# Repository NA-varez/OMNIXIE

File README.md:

# OMNIXIE
Nixie driver board to enable easy inclusion of a Nixie tube into projects. One common driver board to support a wide range of Nixie INdicator Tubes. I love modularity!

Initial sketches, ideas, original project intent was just a nixie clock. But I hated the feeling of desigingn a nixie clock with the nixie driver circuitry as single use for just a clock, when really you should be able to drive a nixie tube anywehere you'd like for displaying numbers. So that's where this inspiration came from

ALSO cnlohr's cnixxie. Particularly his MCU of choice ch32v003 and the accompanying library ch32v003fun and rv003usb inspired the digitally controlled flyback he uses in his design. Really in hopes of learning some skills he demonstrated in his youtube vide.

OMNIXIE is omni beause all of its OMNIXIE_HATs share a common hardware interface to the nixie driver board. Since nixie tubes wildly vary in their footprint, its nice to share a common hardware connection between them all thats what makes it omni. 

The real guts is the ddriver board.
Should be minimal in size such that it doesnt add any more difficult in creating some case for the nixie tube.
Should be relatively efficient like 90% efficiency on the flyback onverter
Should be programmable 
  There should be a software package that comes with the hardware that could easily spin up different functionality

The default program should allow the user of the board to immediatly get the devices to display a synchronized clock.
Via some qwiic connectors. Might have to be a custom i2c interface.

A flyback seemed to be the most suitable approach because of the smallest amount of parts needed for it.

WORK IN PROGRESS.

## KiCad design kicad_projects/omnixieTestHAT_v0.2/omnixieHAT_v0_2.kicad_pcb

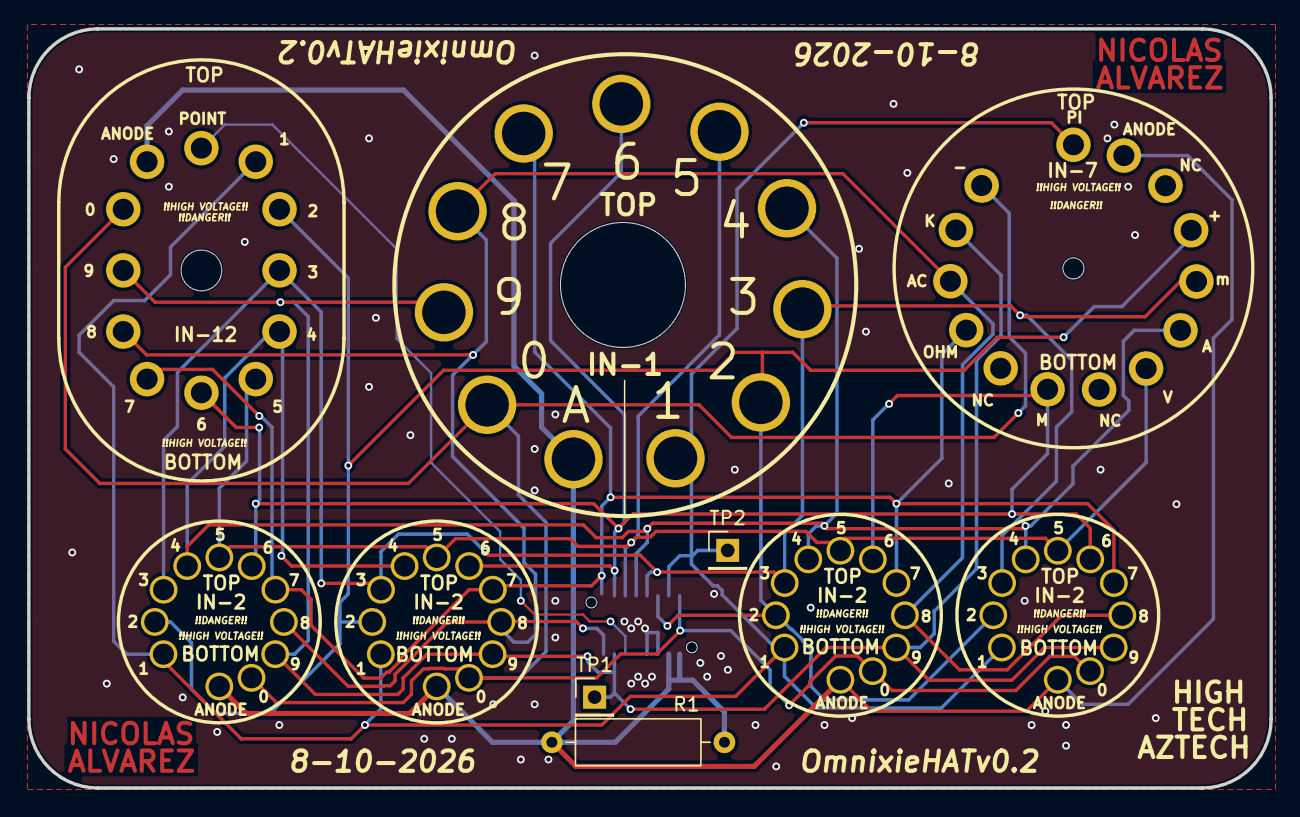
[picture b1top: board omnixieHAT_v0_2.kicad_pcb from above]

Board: 2 copper layers, 91.4 x 55.9 mm, 11 parts (1 on the bottom side), 13 nets.

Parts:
J1: IL-WX-16PB-VF-B-E1000E; IL-WX-16PB-VF-B-E1000E-PINS
N1: IN-1_NIXIE_v1
N2, N5, N6, N7: IN-2
N3: IN-7
N4: IN-12BORIGINAL; IN-12A Nixie
R1: R; R_Axial_DIN0309_L9.0mm_D3.2mm_P12.70mm_Horizontal
TP1: 9; PinHeader_1x01_P2.54mm_Vertical
TP2: 1; PinHeader_1x01_P2.54mm_Vertical

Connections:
CATH0: J1.1, N1.0, N2.0, N3.14 (-), N4.0, N5.0, N6.0, N7.0
CATH1: J1.2, N1.1 (9), N2.1 (9), N3.1 (PI), N4.1, N5.1 (9), N6.1 (9), N7.1 (9), TP2.1 (1_1)
CATH2: J1.3, N1.2 (8), N2.2 (8), N3.4 (+), N4.2, N5.2 (8), N6.2 (8), N7.2 (8)
CATH3: J1.4, N1.3 (7), N2.3 (7), N3.5 (m), N4.3, N5.3 (7), N6.3 (7), N7.3 (7)
CATH4: J1.5, N1.4 (6), N2.4 (6), N3.6 (A), N4.4, N5.4 (6), N6.4 (6), N7.4 (6)
CATH5: J1.6, N1.5, N2.5, N3.7 (V), N4.5, N5.5, N6.5, N7.5
CATH6: J1.7, N1.6 (4), N2.6 (4), N3.9 (M), N4.6, N5.6 (4), N6.6 (4), N7.6 (4)
CATH7: J1.8, N1.7 (3), N2.7 (3), N3.11 (OHM), N4.7, N5.7 (3), N6.7 (3), N7.7 (3)
CATH8: J1.9, N1.8 (2), N2.8 (2), N3.12 (AC), N4.8, N5.8 (2), N6.8 (2), N7.8 (2)
CATH9: J1.10, N1.9 (1), N2.9 (1), N3.13 (K), N4.9, N5.9 (1), N6.9 (1), N7.9 (1), TP1.1 (1_1)
CATHDP: J1.11, N4.DP
GND: J1.13, J1.14
HIGHVOLTAGE: J1.15, J1.16, N1.A, N2.A, N3.2 (A), N4.A, N5.A, N6.A, N7.A, R1.1, R1.2

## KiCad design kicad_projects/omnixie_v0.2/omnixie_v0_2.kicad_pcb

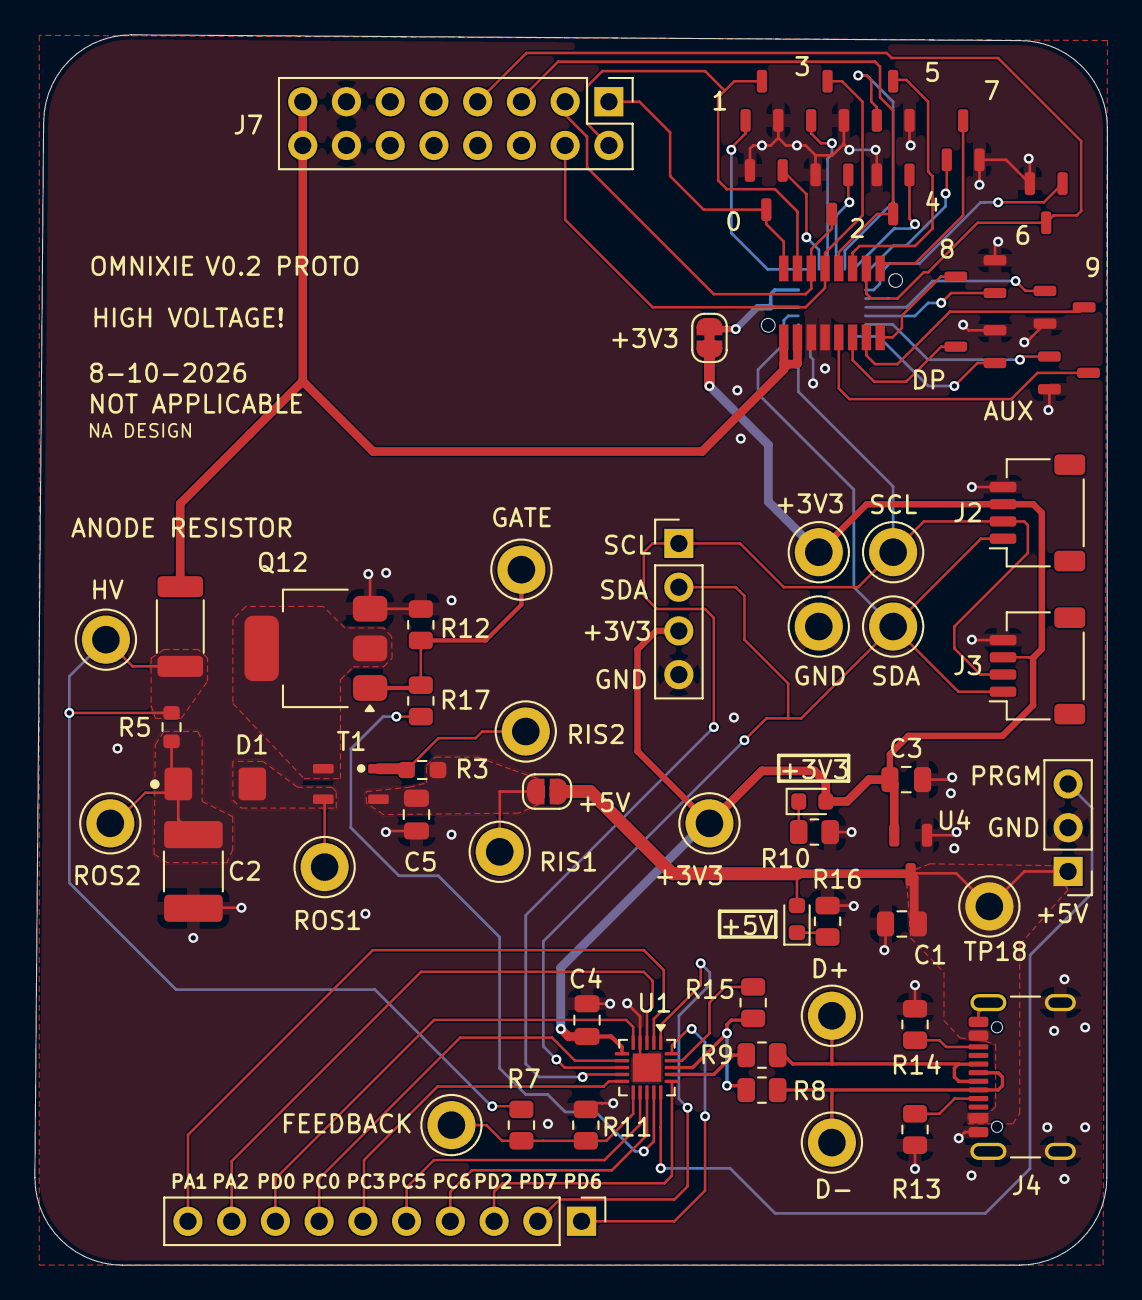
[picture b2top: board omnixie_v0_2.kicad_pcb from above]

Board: 2 copper layers, 62.3 x 71.5 mm, 64 parts (1 on the bottom side), 60 nets.

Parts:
+3V3, +3V3#2: 5005; TestPoint_Keystone_5005-5009_Compact
+5V: GREEN; LED_0603_1608Metric
C1: 10uF; C_0805_2012Metric
C2: 0.22uF; C_1812_4532Metric_Pad1.57x3.40mm_HandSolder
C3, C4, C5: 1uF; C_0805_2012Metric
D1: SK3200AFL-TP; SK3200AFL
D3: GREEN; LED_0603_1608Metric
D+: 5005; TestPoint_Keystone_5005-5009_Compact
D-: 5005; TestPoint_Keystone_5005-5009_Compact
GND: 5005; TestPoint_Keystone_5005-5009_Compact
J1: Conn_01x10; PinHeader_1x10_P2.54mm_Vertical
J2, J3: SM04B-SRSS-TB; JST_SH_SM04B-SRSS-TB_1x04-1MP_P1.00mm_Horizontal
J4: USB4105-GF-A; USB_C_Receptacle_GCT_USB4105-xx-A_16P_TopMnt_Horizontal
J5: Conn_01x04; PinHeader_1x04_P2.54mm_Vertical
J6: Conn_01x02; PinHeader_1x03_P2.54mm_Vertical
J7: Conn_02x08_Counter_Clockwise; PinHeader_2x08_P2.54mm_Vertical
J8: IL-WX-16S-VF-B-E1000E; IL-WX-16S-VF-B-E1000E-SOCKET
JP4: SMT_THERM_JMP; SolderJumper-2_P1.3mm_Bridged_RoundedPad1.0x1.5mm
JP5: TH_THERM_JMP; SolderJumper-2_P1.3mm_Open_RoundedPad1.0x1.5mm
Q0, Q1, Q2, Q3, Q4, Q5, Q6, Q7, Q8, Q9, Q10, Q11: BSS123; SOT-23-3-NO_SILK
Q12: STN1NK60ZL; SOT-223-MiddlePinDrain
R3: 10m; R_0603_1608Metric_Pad0.98x0.95mm_HandSolder
R5: 10m; R_0603_1608Metric
R6: 15k; R_2010_5025Metric
R7: 100k; R_0805_2012Metric
R8, R9: 47; R_0805_2012Metric
R10, R16: 30K; R_0805_2012Metric
R11, R12: 1k; R_0805_2012Metric
R13, R14: 5.1k; R_0805_2012Metric
R15: 1.5k; R_0805_2012Metric
R17: JUMPER; R_0805_2012Metric
RIS1: 5005; TestPoint_Keystone_5005-5009_Compact
SCL: 5005; TestPoint_Keystone_5005-5009_Compact
SDA: 5005; TestPoint_Keystone_5005-5009_Compact
T1: ATB322515-0110; ATB322515
TP6, TP8, TP11, TP12, TP13, TP14, TP18: 5005; TestPoint_Keystone_5005-5009_Compact
U1: CH32V003F4U6; QFN-20-1EP_3x3mm_P0.4mm_EP1.65x1.65mm
U3: PI4IOE5V6416ZDEX; PI4IOE5V6416ZDEX-TQFN24
U4: XC6206P332MR; SOT-23-3-NO_SILK

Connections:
+3V3: +3V3.1 (1_1), +3V3#2.1 (1_1), C3.1, C4.1, D3.2 (A), J2.3, J3.3, J5.3, JP4.1 (A), U1.6 (VDD), U4.2 (VO)
+3V3_JUMP: JP4.2 (B), U3.21 (VDD_P), U3.23 (VDD_I2C)
+5V: +5V.2 (A), C1.1, J4.A4 (VBUS), J4.A9 (VBUS), J4.B4 (VBUS), J4.B9 (VBUS), J6.1, JP5.1 (A), TP18.1 (1_1), U4.3 (VI)
+5V_FLY: C5.1, JP5.2 (B), R3.2, RIS1.1 (1_1), T1.2
/<NO NET>: R3.1, T1.1, TP6.1 (1_1)
/CC1: J4.A5 (CC1), R13.1
/CC2: J4.B5 (CC2), R14.2
/D+_1: R9.2, U1.17 (PD3/A4/T2CH2/AETR/UCTS/T1CH4)
/D-_1: R8.2, R15.2, U1.18 (PD4/A7/UCK/T2CH1ETR/OPO/T1CH4ETR)
/D_1: D1.2 (A), T1.3, TP11.1 (1_1)
/D_2: C2.1, D1.1 (K), R5.2, TP8.1 (1_1)
/HV_1: R5.1, R6.2, R7.1, TP12.1 (1_1)
CATH0: J7.1, J8.1, Q0.3 (D)
CATH1: J7.2, J8.2, Q1.3 (D)
CATH2: J7.3, J8.3, Q2.3 (D)
CATH3: J7.4, J8.4, Q3.3 (D)
CATH4: J7.5, J8.5, Q4.3 (D)
CATH5: J8.6, Q5.3 (D)
CATH6: J7.7, J8.7, Q6.3 (D)
CATH7: J8.8, Q7.3 (D)
CATH8: J8.9, Q8.3 (D)
CATH9: J8.10, Q9.3 (D)
CATHAUX: J8.12, Q10.3 (D)
CATHDP: J8.11, Q11.3 (D)
D+: D+.1 (1_1), J4.A6 (D+), J4.B6 (D+), R9.1
D-: D-.1 (1_1), J4.A7 (D-), J4.B7 (D-), R8.1
DIG_0: Q0.1 (G), U3.2 (IO0_1)
DIG_1: Q1.1 (G), U3.1 (IO0_0)
DIG_2: Q2.1 (G), U3.4 (IO0_3)
DIG_3: Q3.1 (G), U3.3 (IO0_2)
DIG_4: Q4.1 (G), U3.6 (IO0_5)
DIG_5: Q5.1 (G), U3.5 (IO0_4)
DIG_6: Q6.1 (G), U3.8 (IO0_7)
DIG_7: Q7.1 (G), U3.7 (IO0_6)
DIG_8: Q8.1 (G), U3.11 (IO1_1)
DIG_9: Q9.1 (G), U3.10 (IO1_0)
DIG_AUX: Q10.1 (G), U3.12 (IO1_2)
DIG_DP: Q11.1 (G), U3.13 (IO1_3)
DPU: R15.1, U1.19 (PD5/A5/UTX/T2CH4/URX)
GND: C1.2, C2.2, C3.2, C4.2, C5.2, GND.1 (1_1), J2.4, J3.4, J4.A1 (GND), J4.A12 (GND), J4.B1 (GND), J4.B12 (GND), J4.SH (SHIELD), J5.4, J6.2, J7.13, J7.14, J8.13, J8.14, Q0.2 (S), Q1.2 (S), Q2.2 (S), Q3.2 (S), Q4.2 (S), Q5.2 (S), Q6.2 (S), Q7.2 (S), Q8.2 (S), Q9.2 (S), Q10.2 (S), Q11.2 (S), Q12.3 (S), R10.1, R11.2, R12.2, R13.2, R14.1, R16.1, U1.4 (VSS), U1.21 (GND), U3.9 (VSS), U3.18 (ADDR), U4.1 (GND)
HIGHVOLTAGE: J7.15, J7.16, J8.15, J8.16, R6.1
HV_FEEDBACK: R7.2, R11.1, TP13.1 (1_1), U1.11 (PC4/A2/T1CH4/MCO/T1CH1CH2N)
HV_SW: R17.1, U1.14 (PC7/MISO/T1CH2/T2CH2/URTS)
I2C_SCL: J2.2, J3.2, J5.1, SCL.1 (1_1), U1.9 (PC2/SCL/URTS/T1BKIN/AETR/T2CH2/T1ETR), U3.19 (SCL)
I2C_SDA: J2.1, J3.1, J5.2, SDA.1 (1_1), U1.8 (PC1/SDA/NSS/T2CH4/T2CH1ETR/T1BKIN/URX), U3.20 (SDA)
unnamed: +5V.1 (K), R16.2
unnamed: D3.1 (K), R10.2
unnamed: Q12.2 (D), T1.4
unnamed: Q12.1 (G), R12.1, R17.2, TP14.1 (1_1)
PA1: J1.10, U1.2 (PA1/OSCI/A1/T1CH2/OPN0)
PA2: J1.9, U1.3 (PA2/OSCO/A0/T1CH2N/OPP0/AETR2)
PC0: J1.7, U1.7 (PC0/T2CH3/UTX/NSS/T1CH3)
PC3: J1.6, U1.10 (PC3/T1CH3/T1CHIN/UCTS)
PC5: J1.5, U1.12 (PC5/SCK/T1ETR/T2CH1ETR/SCL/UCK/T1CH3)
PC6: J1.4, U1.13 (PC6/MOSI/T1CH1CH3/UCTS/SDA)
PD0: J1.8, U1.5 (PD0/T1CH1N/OPN1/SDA/UTX)
PD2: J1.3, U1.16 (PD2/A3/T1CH1/T2CH3/T1CH2N)
PD6: J1.1, U1.20 (PD6/A7/URX/T2CH3/UTX)
PD7: J1.2, U1.1 (PD7/NRST/T2CH4/OPP1/UCK)
PROGRAM: J6.3, U1.15 (PD1/SWIO/AETR/T1CH3/SCL/URX)

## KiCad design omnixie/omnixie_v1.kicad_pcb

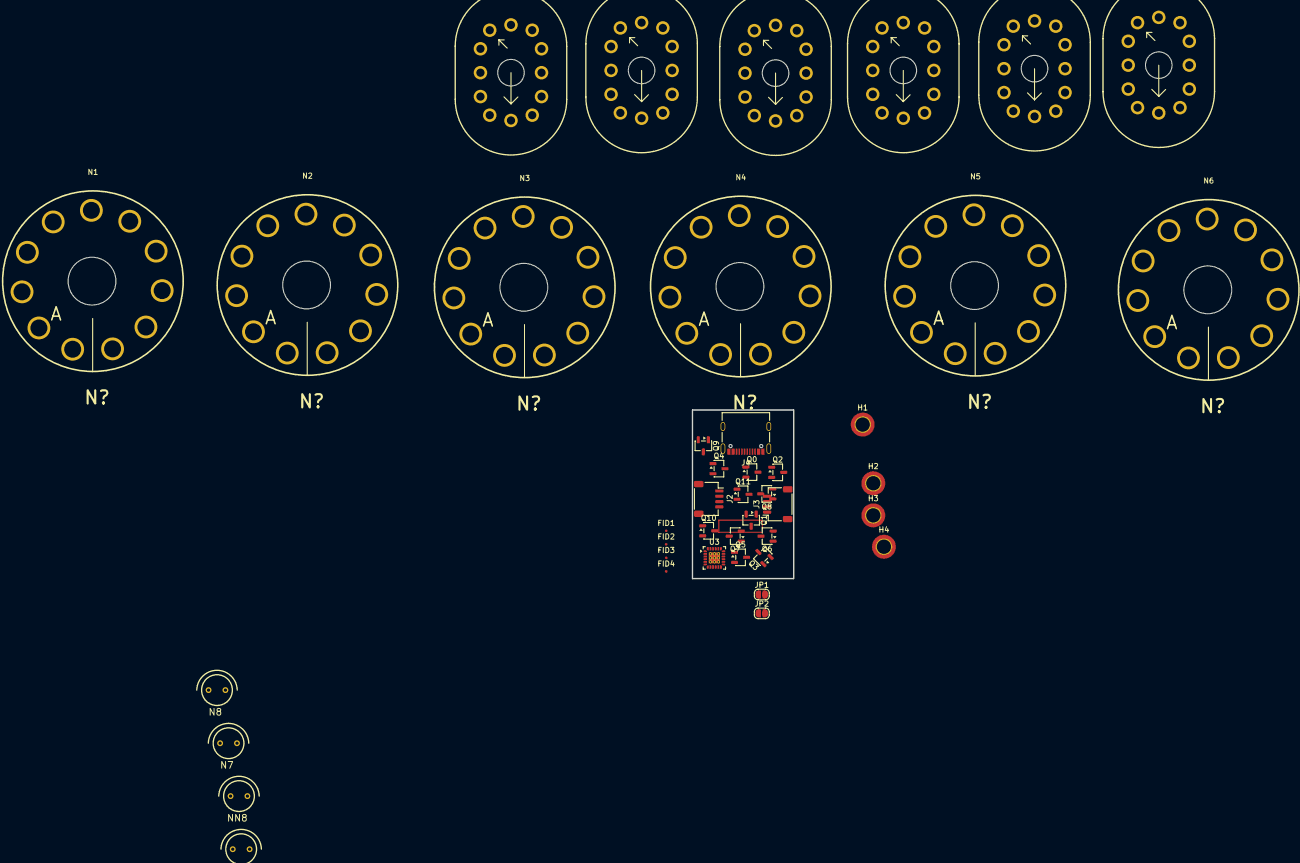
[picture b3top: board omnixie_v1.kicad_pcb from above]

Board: 2 copper layers, 43 parts (1 on the bottom side), 14 nets, no tracks yet.

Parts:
FID1, FID2, FID3, FID4: Fiducial; Fiducial_0.5mm_Mask1mm
H1, H2, H3, H4: MountingHole; MountingHole_2.7mm_M2.5_ISO7380_Pad_TopBottom
J2, J3: Conn_01x04; JST_SH_SM04B-SRSS-TB_1x04-1MP_P1.00mm_Horizontal
J4: USB_C_Receptacle_USB2.0_14P; USB_C_Receptacle_Palconn_UTC16-G
JP1, JP2: TH_THERM_JMP; SolderJumper-2_P1.3mm_Open_RoundedPad1.0x1.5mm
N1, N2, N3, N4, N5, N6: IN-1; IN-1_NIXIE_v1
N7, N8, N9: IN-3; nixies-us-IN-3
NN8: IN-3; nixies-us-IN-3
NX1, NX2, NX3, NX4, NX5, NX6: IN-12BORIGINAL; IN-12A Nixie
Q0, Q1, Q2, Q3, Q4, Q5, Q6, Q7, Q8, Q9, Q10, Q11: Q_NMOS; SOT-23-3
U1: CH32V003F4U6; QFN-20-1EP_3x3mm_P0.4mm_EP1.65x1.65mm
U3: TQFN-24-1EP_4x4mm_P0.5mm_EP2.1x2.1mm_ThermalVias

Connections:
CATH0: N1.0, N2.0, Q0.3 (D)
CATH1: N1.1, N2.1, NX1.1, Q1.3 (D)
CATH2: N1.2, N2.2, NX1.2, Q2.3 (D)
CATH3: N1.3, N2.3, NX1.3, Q3.3 (D)
CATH4: N1.4, N2.4, NX1.4, Q4.3 (D)
CATH5: N1.5, N2.5, NX1.5, Q5.3 (D)
CATH6: N1.6, N2.6, NX1.6, Q6.3 (D)
CATH7: N1.7, N2.7, NX1.7, Q7.3 (D)
CATH8: N1.8, N2.8, NX1.8, Q8.3 (D)
CATH9: N1.9, N2.9, NX1.9, Q9.3 (D)
GND: Q0.2 (S), Q1.2 (S), Q2.2 (S), Q3.2 (S), Q4.2 (S), Q5.2 (S), Q6.2 (S), Q7.2 (S), Q8.2 (S), Q9.2 (S), Q10.2 (S), Q11.2 (S), U1.4 (VSS), U1.21 (GND)
unnamed: J4.A1 (GND), J4.A12 (GND), J4.B1 (GND), J4.B12 (GND)
unnamed: J4.A4 (VBUS), J4.A9 (VBUS), J4.B4 (VBUS), J4.B9 (VBUS)
unnamed: JP1.2 (B), JP2.2 (B)

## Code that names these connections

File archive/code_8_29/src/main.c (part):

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	RCC->APB1PRSTR |= RCC_APB1Periph_TIM2;
	RCC->APB1PRSTR &= ~RCC_APB1Periph_TIM2;

	// PD7 will be used as Timer 2, Channel 4 Configure timer 2 to enable this.
	//TIM2->SWEVGR = 0x0001; 			//TIM_PSCReloadMode_Immediate;

	TIM2->PSC = 0x0020;
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static void SetupADC()
{
	// Configure ADC.
	// PD4 is analog input chl 7
	GPIOD->CFGLR &= ~(0xf<<(4*4));	// CNF = 00: Analog, MODE = 00: Input
	
	// Reset the ADC to init all regs
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
	GPIOD->CFGLR = 
		(GPIO_Speed_10MHz | GPIO_CNF_OUT_PP)<<(4*6) | // GPIO D6 Debug
		(GPIO_Speed_10MHz | GPIO_CNF_OUT_PP_AF)<<(4*7) | // DIG_AUX  (TIM2CH4)
		(GPIO_Speed_10MHz | GPIO_CNF_OUT_PP)<<(4*3) | // DIG_9
		(GPIO_Speed_10MHz | GPIO_CNF_OUT_PP)<<(4*2) | // DIG_8
		(GPIO_Speed_10MHz | GPIO_CNF_IN_FLOATING)<<(4*1) | // PGM Floats.
		(GPIO_Speed_10MHz | GPIO_CNF_OUT_PP)<<(4*0);  // DIG_DOT

	GPIOC->CFGLR = 
		(GPIO_Speed_10MHz | GPIO_CNF_OUT_PP)<<(4*0) | // DIG_0
		(GPIO_Speed_10MHz | GPIO_CNF_OUT_PP)<<(4*1) | // DIG_1
		(GPIO_Speed_10MHz | GPIO_CNF_OUT_PP)<<(4*2) | // DIG_2
		(GPIO_Speed_10MHz | GPIO_CNF_OUT_PP)<<(4*3) | // DIG_3
		(GPIO_Speed_10MHz | GPIO_CNF_OUT_PP)<<(4*4) | // DIG_4
		(GPIO_Speed_10MHz | GPIO_CNF_OUT_PP)<<(4*5) | // DIG_5
		(GPIO_Speed_10MHz | GPIO_CNF_OUT_PP)<<(4*6) | // DIG_6
		(GPIO_Speed_10MHz | GPIO_CNF_OUT_PP)<<(4*7);  // DIG_7


	GPIOA->CFGLR =
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
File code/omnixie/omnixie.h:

// #include "ch32fun.h"
// #include <string.h>
// #include "rv003usb.h"


#define PIN_HV_GATE_DRIVE		//PC7
#define PIN_HV_FEEDBACK		//PC4
#define ANALOG_HV_FEEDBACK	2		//PC4 Analog 2

#define PIN_SDA			//PC1
#define PIN_SCL 		//PC2

void omnixie_init() {
	// configure

	// init

	// default states
}

/**
 * TODO
 * 
 * How bout you learn how to program a PID in firmware
 * Efficient PID code in firmware. Or at least get the bones
 * understand the bones then use cnixxie to do the optimizations
 * 
 * Driver for I2C GPIO Expander
 * 
 * Try simulating PID control on-chip? MATLAB is what this is for really
 * 
 * HV PID control
 * 	Get 200V max
 * 	Use T1Ch2 or T2Ch2
 * 	Feedback via A2
 * 
 * 
 */

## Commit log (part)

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2025-11-23 Adding files:
2025-12-04 commiting last work i did
2025-12-08 changed folder names, started bom
2025-12-18 component selection nearly done
2025-12-18 component placement commencing
2025-12-18 more component placement
2025-12-25 reworking the board. Its a prototype not production ready
2025-12-25 new component placement pretty much done
2025-12-28 home from christmas in vegas
2026-01-10 separated proto from production version with actual footprints
2026-01-12 p much done, no nixie hat board though
2026-03-26 remaining files i forgor
2026-04-18 initial commit readme
2026-04-19 Update README with flyback approach details
    Added information about using a flyback approach for the project.
2026-04-20 adding code folder
2026-05-26 phil's lab controller added. not working.
2026-06-06 removed unneccesary stuff

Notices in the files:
archive/code_8_29/src/main.c:
Copyright 2023 <>< Charles Lohr, under the MIT-X11 license or NewBSD
